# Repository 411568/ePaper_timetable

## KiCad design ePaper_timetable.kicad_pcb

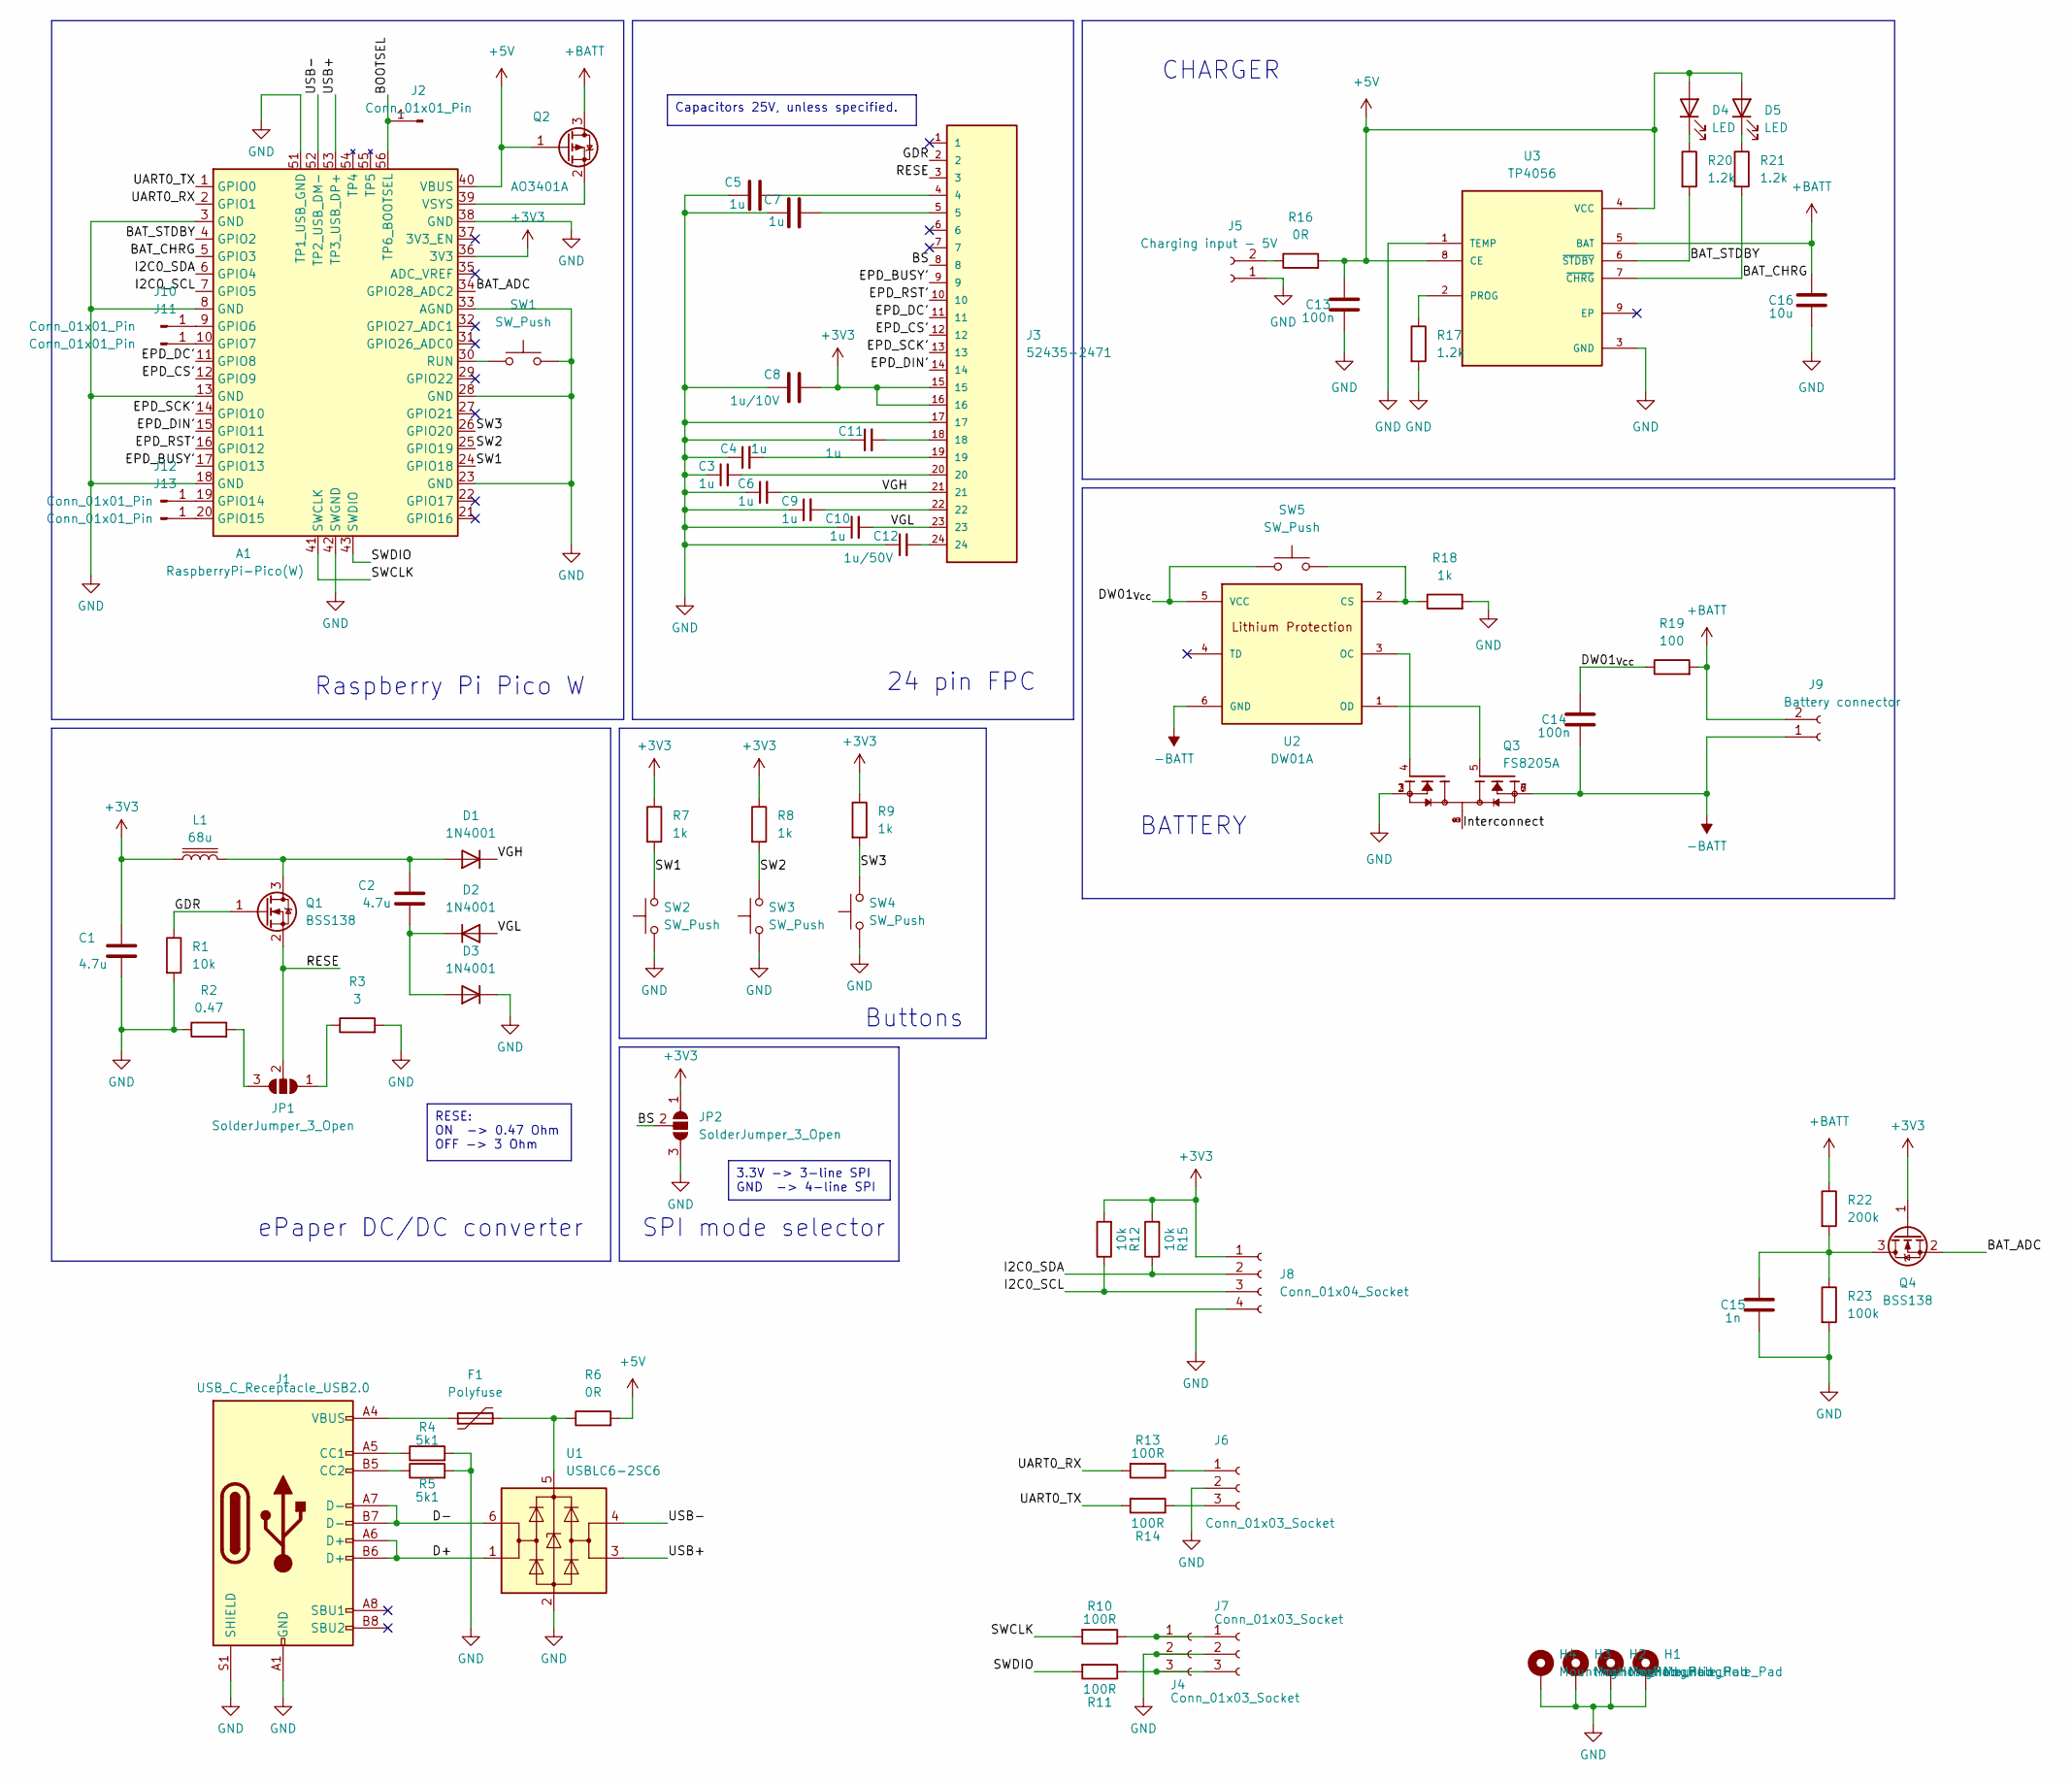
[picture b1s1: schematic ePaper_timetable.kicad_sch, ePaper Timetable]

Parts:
A1: RaspberryPi-Pico(W); Raspberry_Pi_Pico_W_SMT
C1, C2: 4.7u; C_0805_2012Metric_Pad1.18x1.45mm_HandSolder
C3, C4, C5, C6, C7, C9, C10, C11: 1u; C_0805_2012Metric_Pad1.18x1.45mm_HandSolder
C8: 1u/10V; C_0805_2012Metric_Pad1.18x1.45mm_HandSolder
C12: 1u/50V; C_0805_2012Metric_Pad1.18x1.45mm_HandSolder
C13, C14: 100n; C_0805_2012Metric_Pad1.18x1.45mm_HandSolder
C15: 1n; C_0805_2012Metric_Pad1.18x1.45mm_HandSolder
C16: 10u; C_0805_2012Metric_Pad1.18x1.45mm_HandSolder
D1, D2, D3: 1N4001; D_SOD-123
D4, D5: LED; LED_0805_2012Metric_Pad1.15x1.40mm_HandSolder
F1: Polyfuse; Fuse_1812_4532Metric_Pad1.30x3.40mm_HandSolder
H1, H2, H3, H4: MountingHole_Pad; MountingHole_3.2mm_M3_Pad
J1: USB_C_Receptacle_USB2.0; USB_C_Receptacle_GCT_USB4105-xx-A_16P_TopMnt_Horizontal
J2, J10, J11, J12, J13: Conn_01x01_Pin; SolderWirePad_1x01_SMD_1x2mm
J3: 52435-2471; MOLEX_52435-2471
J4, J6: Conn_01x03_Socket; PinSocket_1x03_P2.54mm_Vertical
J5: Charging input - 5V; PhoenixContact_MC_1,5_2-G-3.81_1x02_P3.81mm_Horizontal
J7: Conn_01x03_Socket; JST_SH_BM03B-SRSS-TB_1x03-1MP_P1.00mm_Vertical
J8: Conn_01x04_Socket; PinSocket_1x04_P2.54mm_Vertical
J9: Battery connector; PinSocket_1x02_P2.54mm_Vertical
JP1, JP2: SolderJumper_3_Open; SolderJumper-3_P1.3mm_Open_RoundedPad1.0x1.5mm_NumberLabels
L1: 68u; L_Changjiang_FNR6045S
Q1, Q4: BSS138; SOT-23
Q2: AO3401A; SOT-23
Q3: FS8205A; TSSOP-8_4.4x3mm_P0.65mm; PARTREV 1.7
R1, R12, R15: 10k; R_0805_2012Metric_Pad1.20x1.40mm_HandSolder
R2: 0.47; R_0805_2012Metric_Pad1.20x1.40mm_HandSolder
R3: 3; R_0805_2012Metric_Pad1.20x1.40mm_HandSolder
R4, R5: 5k1; R_0805_2012Metric_Pad1.20x1.40mm_HandSolder
R6, R16: 0R; R_1206_3216Metric_Pad1.30x1.75mm_HandSolder
R7, R8, R9, R18: 1k; R_0805_2012Metric_Pad1.20x1.40mm_HandSolder
R10, R11, R13, R14: 100R; R_0805_2012Metric_Pad1.20x1.40mm_HandSolder
R17, R20, R21: 1.2k; R_0805_2012Metric_Pad1.20x1.40mm_HandSolder
R19: 100; R_0805_2012Metric_Pad1.20x1.40mm_HandSolder
R22: 200k; R_0805_2012Metric_Pad1.20x1.40mm_HandSolder
R23: 100k; R_0805_2012Metric_Pad1.20x1.40mm_HandSolder
SW1, SW5: SW_Push; SW_Tactile_SPST_NO_Straight_CK_PTS636Sx25SMTRLFS
SW2, SW3, SW4: SW_Push; SW_PUSH_6mm_H7.3mm
U1: USBLC6-2SC6; SOT-23-6
U2: DW01A; SOT-23-6_Handsoldering; M_PART_NUMBER DW01A
U3: TP4056; HTSOP-8-1EP_3.9x4.9mm_P1.27mm_EP2.4x3.2mm

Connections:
+3V3: A1.36 (3V3), C1.2, C8.2, J3.15, J3.16, J8.1, JP2.1 (A), L1.1, Q4.1 (G), R7.1, R8.1, R9.1, R12.2, R15.2
+5V: A1.40 (VBUS), C13.2, D4.2 (A), D5.2 (A), Q2.1 (G), R6.2, R16.2, U3.4 (VCC), U3.8 (CE)
+BATT: C16.2, J9.2, Q2.3 (D), R19.2, R22.1, U3.5 (BAT)
-BATT: C14.1, J9.1, Q3.6, Q3.7, U2.6 (GND)
/BAT_ADC: A1.34 (GPIO28_ADC2), Q4.2 (S)
/BAT_CHRG: A1.5 (GPIO3), R21.2, U3.7 (~CHRG)
/BAT_STDBY: A1.4 (GPIO2), R20.2, U3.6 (~STDBY)
/BOOTSEL: A1.56 (TP6_BOOTSEL), J2.1
/BS: J3.8, JP2.2 (C)
/D+: J1.A6 (D+), J1.B6 (D+), U1.1 (I/O1)
/D-: J1.A7 (D-), J1.B7 (D-), U1.6 (I/O1)
/DW01_{Vcc}: C14.2, R19.1, SW5.1, U2.5 (VCC)
/EPD_BUSY': A1.17 (GPIO13), J3.9
/EPD_CS': A1.12 (GPIO9), J3.12
/EPD_DC': A1.11 (GPIO8), J3.11
/EPD_DIN': A1.15 (GPIO11), J3.14
/EPD_RST': A1.16 (GPIO12), J3.10
/EPD_SCK': A1.14 (GPIO10), J3.13
/GDR: J3.2, Q1.1 (G), R1.1
/I2C0_SCL: A1.7 (GPIO5), J8.3, R12.1
/I2C0_SDA: A1.6 (GPIO4), J8.2, R15.1
/Interconnect: Q3.1, Q3.8
/RESE: J3.3, JP1.2 (C), Q1.2 (S)
/SW1: A1.24 (GPIO18), R7.2, SW2.2
/SW2: A1.25 (GPIO19), R8.2, SW3.2
/SW3: A1.26 (GPIO20), R9.2, SW4.2
/SWCLK: A1.41 (SWCLK), R10.2
/SWDIO: A1.43 (SWDIO), R11.2
/UART0_RX: A1.2 (GPIO1), R13.2
/UART0_TX: A1.1 (GPIO0), R14.2
/USB+: A1.53 (TP3_USB_DP+), U1.3 (I/O2)
/USB-: A1.52 (TP2_USB_DM-), U1.4 (I/O2)
/VGH: C6.2, D1.1 (K), J3.21
/VGL: C10.2, D2.2 (A), J3.23
GND: A1.3 (GND), A1.8 (GND), A1.13 (GND), A1.18 (GND), A1.23 (GND), A1.28 (GND), A1.33 (AGND), A1.38 (GND), A1.42 (SWGND), A1.51 (TP1_USB_GND), C1.1, C3.1, C4.1, C5.1, C6.1, C7.1, C8.1, C9.1, C10.1, C11.1, C12.1, C13.1, C15.1, C16.1, D3.1 (K), H1.1, H2.1, H3.1, H4.1, J1.A1 (GND), J1.A12 (GND), J1.B1 (GND), J1.B12 (GND), J1.S1 (SHIELD), J3.17, J4.2, J5.1, J6.2, J7.2, J8.4, JP2.3 (B), Q3.2, Q3.3, R1.2, R2.1, R3.2, R4.2, R5.2, R17.2, R18.2, R23.2, SW1.2, SW2.1, SW3.1, SW4.1, U1.2 (GND), U3.1 (TEMP), U3.3 (GND)
unnamed: A1.9 (GPIO6), J10.1
unnamed: A1.10 (GPIO7), J11.1
unnamed: A1.19 (GPIO14), J12.1
unnamed: A1.20 (GPIO15), J13.1
unnamed: A1.30 (RUN), SW1.1
unnamed: A1.39 (VSYS), Q2.2 (S)
unnamed: C3.2, J3.20
unnamed: C4.2, J3.19
unnamed: C5.2, J3.4
unnamed: C7.2, J3.5
unnamed: C9.2, J3.22
unnamed: C11.2, J3.18
unnamed: C12.2, J3.24
unnamed: C2.2, D1.2 (A), L1.2, Q1.3 (D)
unnamed: C2.1, D2.1 (K), D3.2 (A)
unnamed: D4.1 (K), R20.1
unnamed: D5.1 (K), R21.1
unnamed: F1.1, J1.A4 (VBUS), J1.A9 (VBUS), J1.B4 (VBUS), J1.B9 (VBUS)
unnamed: J1.A5 (CC1), R4.1
unnamed: J1.B5 (CC2), R5.1
unnamed: J4.1, J7.1, R10.1
unnamed: J4.3, J7.3, R11.1
unnamed: J5.2, R16.1
unnamed: J6.1, R13.1
unnamed: J6.3, R14.1
unnamed: JP1.1 (A), R3.1
unnamed: JP1.3 (B), R2.2
unnamed: C15.2, Q4.3 (D), R22.2, R23.1
unnamed: F1.2, R6.1, U1.5 (VBUS)
unnamed: R18.1, SW5.2, U2.2 (CS)
unnamed: Q3.4, U2.3 (OC)
unnamed: Q3.5, U2.1 (OD)
unnamed: R17.1, U3.2 (PROG)

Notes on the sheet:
Capacitors 25V, unless specified.
3.3V -> 3-line SPI GND -> 4-line SPI
RESE: ON -> 0.47 Ohm OFF -> 3 Ohm
CHARGER
ePaper DC/DC converter
SPI mode selector
24 pin FPC
BATTERY
Raspberry Pi Pico W
Buttons

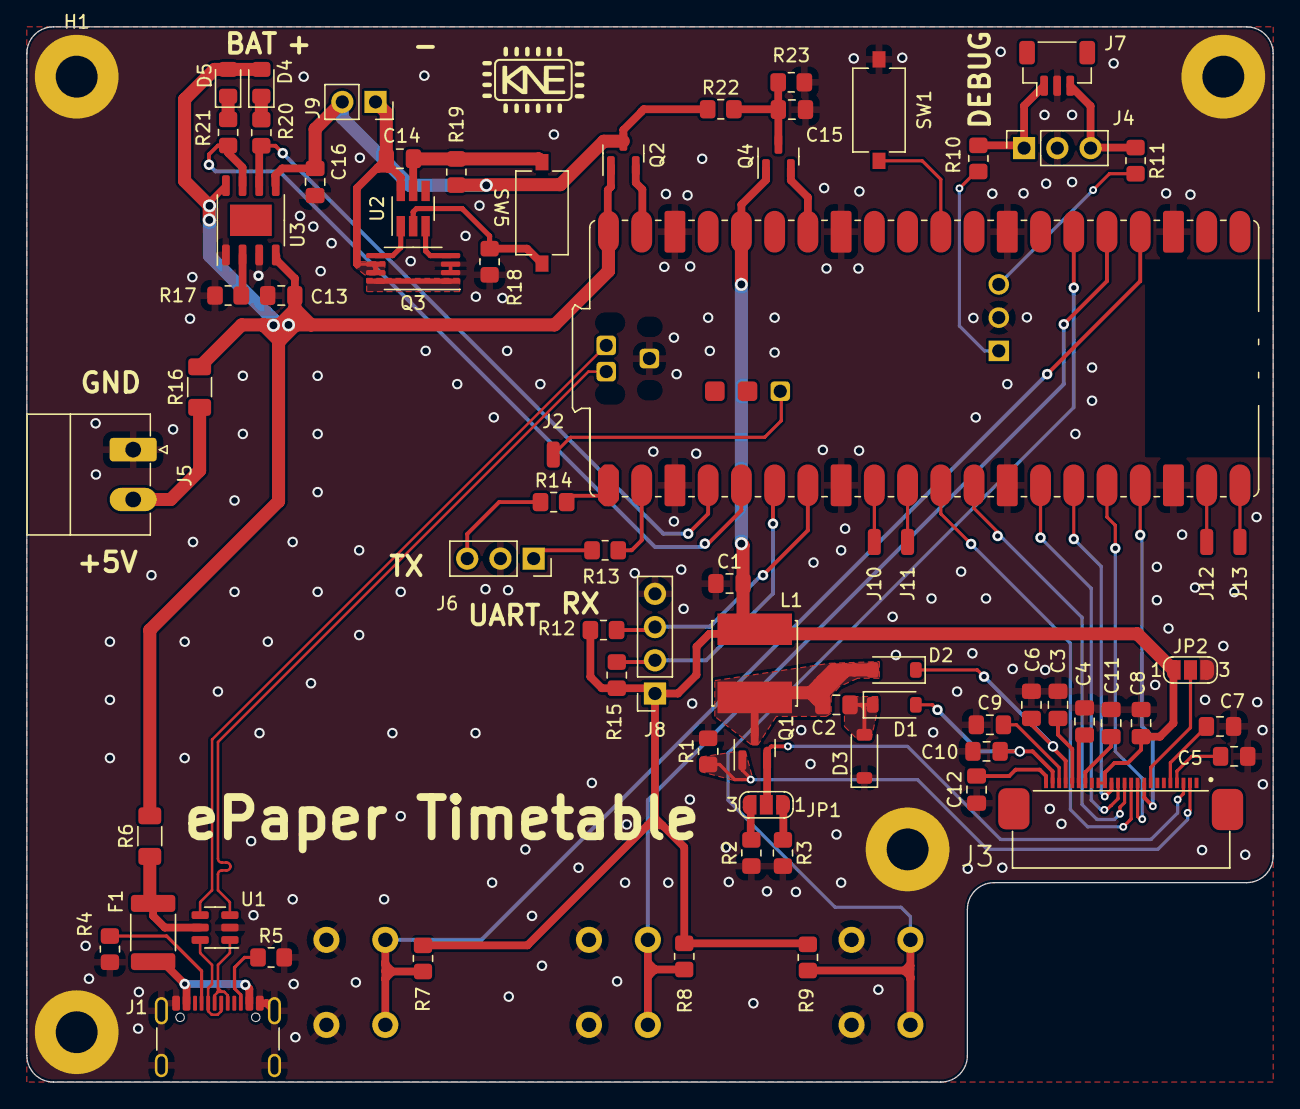
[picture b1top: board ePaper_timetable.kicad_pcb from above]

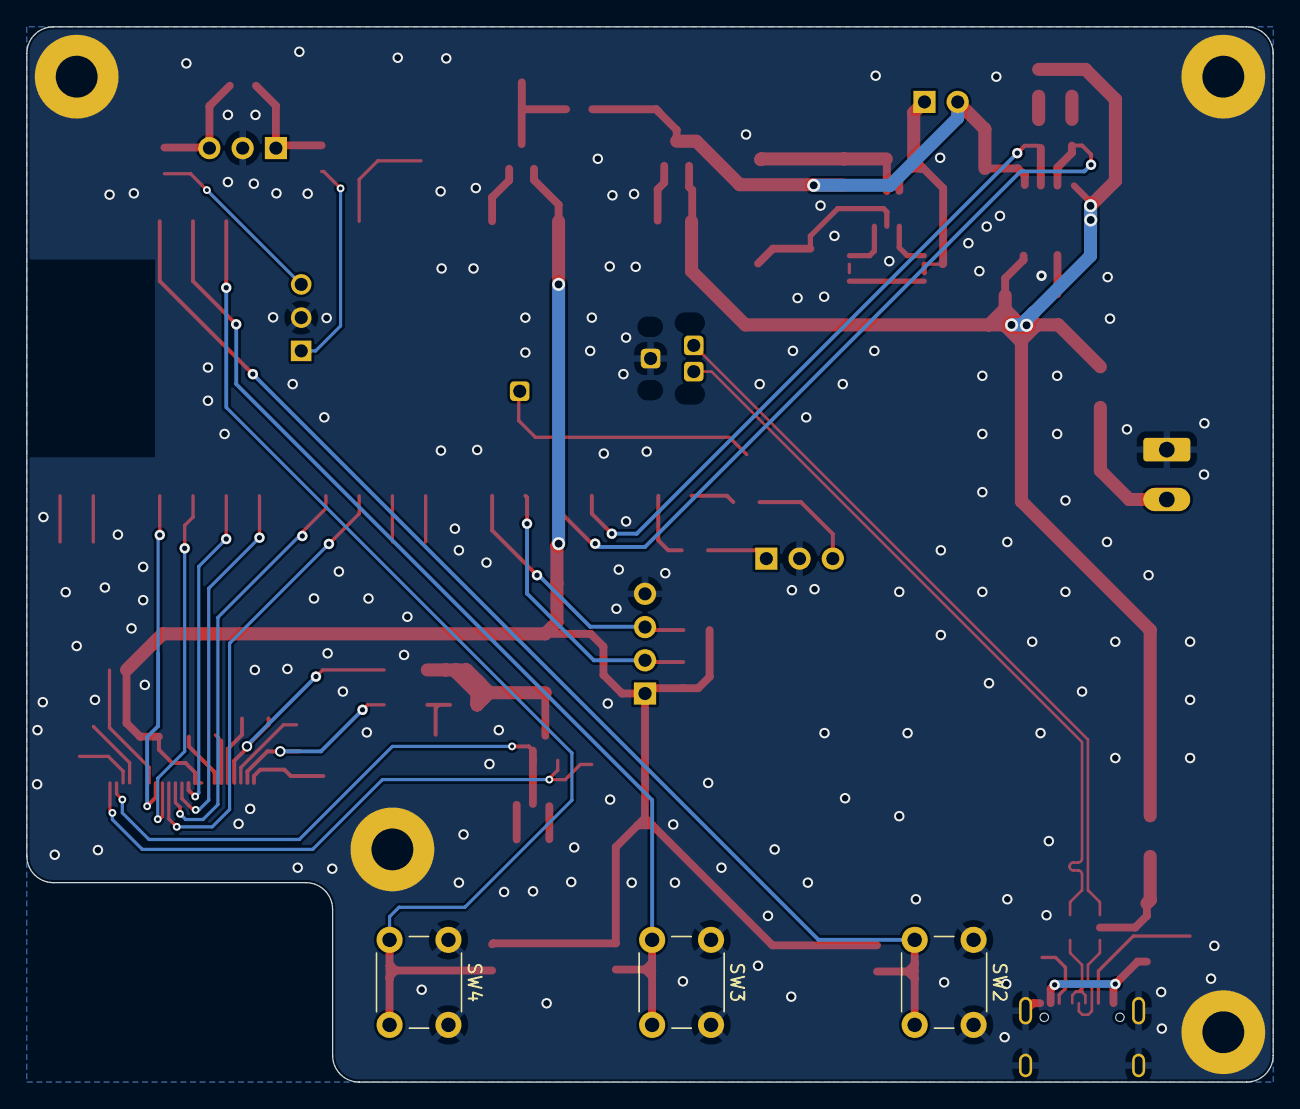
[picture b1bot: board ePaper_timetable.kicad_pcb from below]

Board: 2 copper layers, 95.2 x 80.6 mm, 78 parts (3 on the bottom side), 68 nets.

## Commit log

2023-11-29 kicad project
2023-11-29 first schematic
2023-12-06 reference board
2023-12-06 schematic update: added footprints
2023-12-06 charging circuit footprints added
2023-12-06 display 3d model added
2023-12-06 datasheet
2023-12-06 Adding FPC footprints libraries.
2023-12-06 removed autosave
2023-12-06 fixed pcb - not saved previously
2023-12-06 add gitignore
2023-12-06 update gitignore
2023-12-08 update sch and lib
2023-12-08 update sch and pcb
2023-12-14 fpc connector fix
2023-12-14 layout started
2023-12-15 layout proposition
2023-12-16 prepared for review
2023-12-17 minor changes
2023-12-17 gerbers generated
2023-12-21 move gerber files
2023-12-21 cosmetic
2024-01-02 step file generated
2024-01-02 added 3d models
2024-01-10 Create Pico SDK project
2024-01-10 add waveshare example
2024-01-10 clean .gitignore
2024-01-11 json
2024-01-22 cmake update
2024-01-23 python ical parser
2024-01-24 bitmap testing
2024-01-24 add bmp and h image
2024-01-24 new headers
2024-01-24 mirror and rotate image
2024-01-24 add new images
2024-01-24 update kne image
2024-01-24 update kne
2024-01-24 we did it
